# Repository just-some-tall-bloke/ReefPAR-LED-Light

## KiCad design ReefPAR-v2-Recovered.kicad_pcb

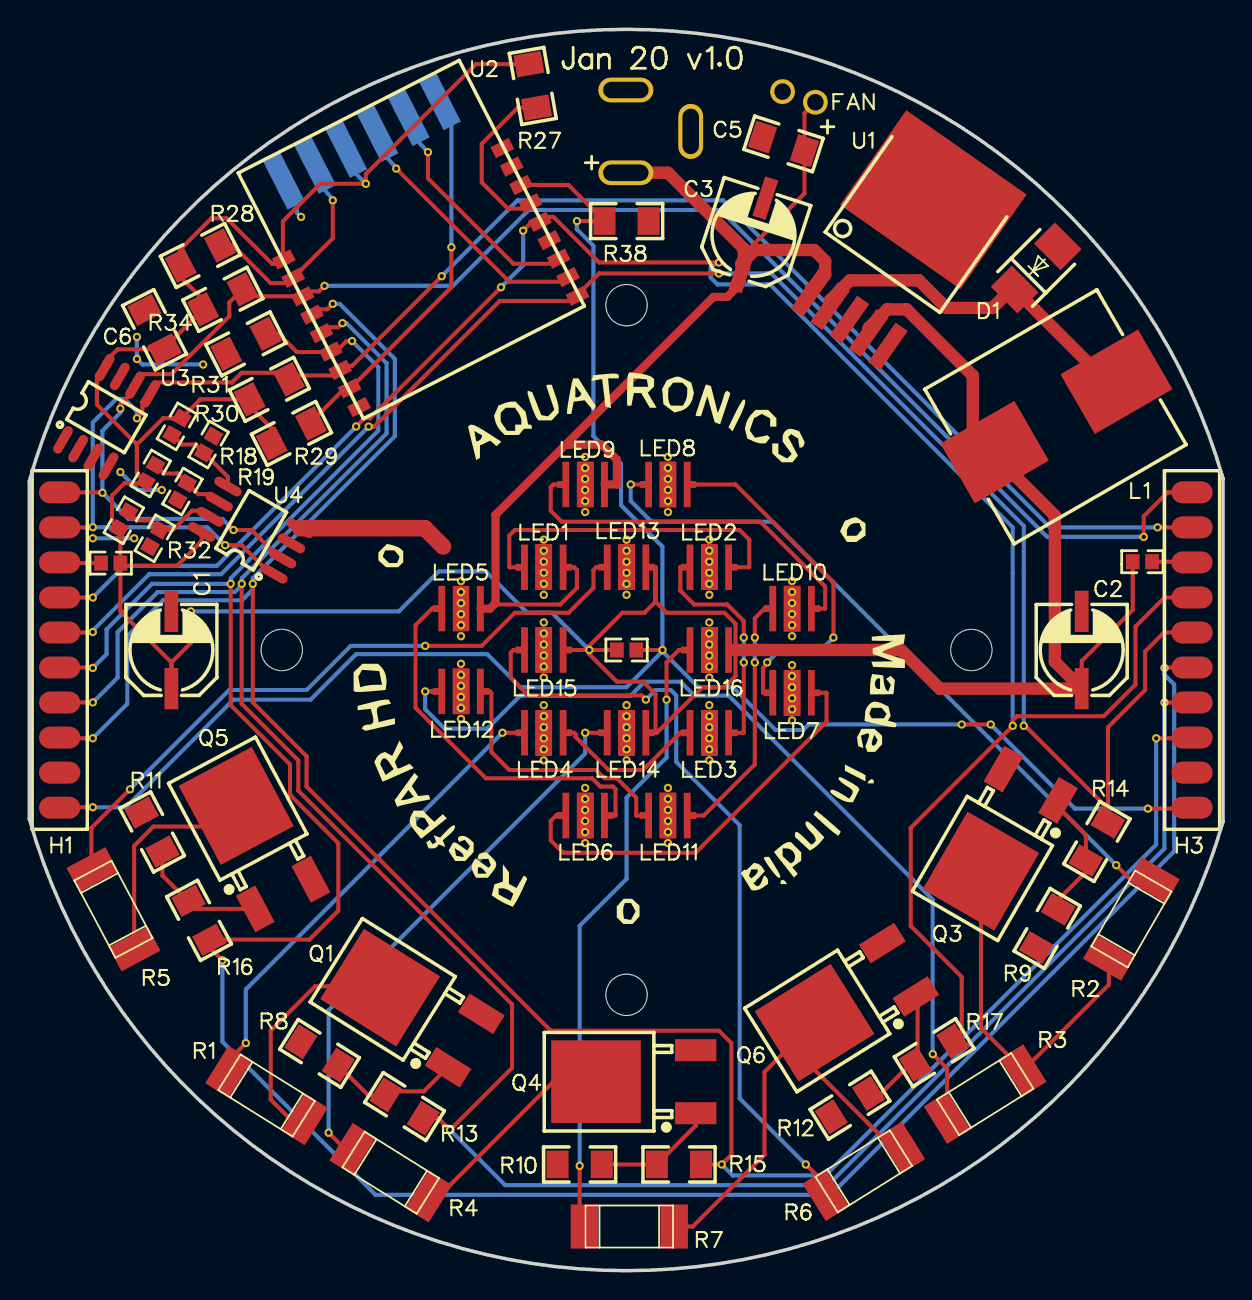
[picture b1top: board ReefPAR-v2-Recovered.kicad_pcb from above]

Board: 2 copper layers, 86.5 x 90.0 mm, 181 parts (0 on the bottom side), 39 nets, no tracks yet.

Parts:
H1, H2, H3, H4: MountingHole
H5, H6, H7, H8, H9, H10, H11, H12, H13, H14, H15, H16, H17, H18, H19, H20, H21, H22, H23, H24, H25, H26, H27, H28, H29, H30, H31, H32, H33, H34, H35, H36, H37, H38, H39, H40, H41, H42, H43, H44, H45, H46, H47, H48, H49, H50, H51, H52, H53, H54, H55, H56, H57, H58, H59, H60, H61, H62, H63, H64, H65, H66, H67, H68, H69, H70, H71, H72, H73, H74, H75, H76, H77, H78, H79, H80, H81, H82, H83, H84, H85, H86, H87, H88, H89, H90, H91, H92, H93, H94, H95, H96, H97, H98, H99, H100, H101, H102, H103, H104, H105, H106, H107, H108, H109, H110, H111, H112, H113, H114, H115, H116, H117, H118, H119, H120, H121, H122, H123, H124, H125, H126, H127, H128, H129, H130, H131, H132, H133, H134, H135, H136, H137, H138, H139, H140, H141, H142, H143, H144, H145, H146, H147, H148, H149, H150, H151, H152, H153, H154, H155, H156, H157, H158, H159, H160, H161, H162, H163, H164, H165, H166, H167, H168, H169, H170, H171, H172, H173, H174, H175, H176: ViaHole
H177, H178: PlatedHole
H179, H180, H181: PlatedSlot

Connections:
RECOVERED_002: H178.1, H179.1
RECOVERED_003: H40.1, H53.1, H64.1, H161.1, H176.1
RECOVERED_004: H27.1, H43.1, H60.1, H170.1
RECOVERED_005: H41.1, H44.1, H54.1, H55.1, H56.1, H173.1
RECOVERED_006: H23.1, H38.1, H57.1, H158.1, H174.1
RECOVERED_007: H25.1, H39.1, H59.1, H171.1, H175.1
RECOVERED_008: H24.1, H37.1, H58.1, H159.1, H172.1
RECOVERED_010: H21.1, H26.1, H42.1, H61.1, H62.1, H169.1
RECOVERED_011: H36.1, H52.1, H63.1, H157.1, H160.1
RECOVERED_012: H17.1, H22.1, H29.1
RECOVERED_017: H32.1, H33.1
RECOVERED_018: H11.1, H48.1
RECOVERED_020: H10.1, H51.1
RECOVERED_022: H31.1, H35.1
RECOVERED_029: H6.1, H46.1
RECOVERED_030: H7.1, H49.1
RECOVERED_031: H30.1, H34.1
RECOVERED_032: H8.1, H50.1
RECOVERED_034: H5.1, H47.1
RECOVERED_035: H9.1, H45.1
RECOVERED_057: H104.1, H105.1, H106.1, H107.1
RECOVERED_058: H116.1, H117.1, H118.1, H119.1
RECOVERED_059: H80.1, H81.1, H82.1, H83.1
RECOVERED_060: H122.1, H123.1, H124.1, H125.1
RECOVERED_061: H152.1, H153.1, H154.1, H155.1
RECOVERED_062: H140.1, H141.1, H142.1, H143.1
RECOVERED_063: H92.1, H93.1, H94.1, H95.1
RECOVERED_064: H68.1, H69.1, H70.1, H71.1
RECOVERED_065: H12.1, H13.1, H14.1, H28.1
RECOVERED_066: H98.1, H99.1, H100.1, H101.1
RECOVERED_067: H134.1, H135.1, H136.1, H137.1
RECOVERED_068: H146.1, H147.1, H148.1, H149.1
RECOVERED_069: H86.1, H87.1, H88.1, H89.1
RECOVERED_070: H74.1, H75.1, H76.1, H77.1
RECOVERED_071: H128.1, H129.1, H130.1, H131.1
RECOVERED_083: H110.1, H111.1, H112.1, H113.1
RECOVERED_135: H162.1, H163.1, H164.1
RECOVERED_136: H165.1, H166.1
RECOVERED_137: H167.1, H168.1
